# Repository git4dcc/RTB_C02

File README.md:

# RTB_C02

My C02 module is designed to trace DCC Railcom traffic for decoder debugging and development purposes. In particular the Railcom capture is an important feature and helps to validate if a decoders is RCN-217 compliant. The C02 uses the Vt100 terminal emulation control codes for its user interface. Therefore a VT100 capeable terminal program is a must (e.g. putty, teraterm). The USB interface is galvanically isolated from the DCC track potential.

<details>
<summary>User Guides</summary>

- [User Guide - DE](https://rtb4dcc.de/DPM_User_Guide_de)<br>
- User Guide - EN

</details>

<br>

# Hardware
My current PCB layout uses SMD footprints with 0.5mm pitch and mostly 0603 but some 0402 parts. Reflow soldering is my recommendation, but with some experience handsoldering may also be possible.

## PCB
- 4-layer PCB, FR4, 1.6mm
- CPU: mega328pb
- USB: FT232x (Mini-B)
- DC/DC: NME0505SC (or compatible)

## Kicad
[Schematic](doc/C02_schematic.pdf) | [Layout](doc/C02_layout.pdf) | [Gerber](gerber/)

<details>
<summary>Dependency</summary>
<br>
  
:yellow_circle: Requires my Kicad project library [RTB_SamacSys](/../../../../git4dcc/RTB_SamacSys) in the same directory tree.

</details>

## Firmware
Filename structure: { **pcb** }{ **code** }{ **version** }.hex

Example: **C02F0001**.hex

|   | Description |
| --- | --- |
| **pcb** | Name of matching hardware (**C02**) |
| **code** | Type of code contained (**R**=rom, **B**=bootloader, **F**=flash, **U**=bld update, **P**=UPDI/SPI factory code) |
| **version** | Release version (**####**) |

## ISP
The fuse settings as well as the P-code (C02Pxxxx.hex) has to be installed by using the ISP.<br>

<details>
<summary>Details</summary>
<br>

> **CAUTION:** Before connecting the ISP, the jumper next to the ISP 6-pin interface must be closed (yellow jumper on picture).

<br>

| Fuses Setting | Bootloader Install |
| --- | --- |
|||

</details>

## Bootloader
Subsequent main code updates can be done via uploading the new firmware (C02Fxxxx.hex) file to the bootloader console prompt.<br>

<details>
<summary>Details</summary>

- press F1 to switch to console screen
- press ^b (ctrl-b) to enter bootloader
- upload the firmware file (C02Fxxxx.hex)
- press x to exit the bootloader

</details>

# Software
Operating the C02 is within the terminal window.
## Terminal screens
Below some example screens of the different functional sections. The screens (called aspects) can be switched by pressing F1-F7.
All screens are updated in real-time speed, ensuring always up-to-date information shown.

| Aspect | Example |
| --- | --- |
| **F1:** Console prompt. |  |
| **F2:** DCC/Railcom line by line real-time trace. |  |
| **F3:** DCC/Railcom decoder payload |  |
| **F4:** DCC/Railcom timing<br> |  |
| **F5:** DCC command set |  |
| **F6:** Railcom response set |  |

# Images
This is how the PCB looks like.<br><br>

# YouTube
Some short videos to see the DCC/Railcom logger in action.<br><br>

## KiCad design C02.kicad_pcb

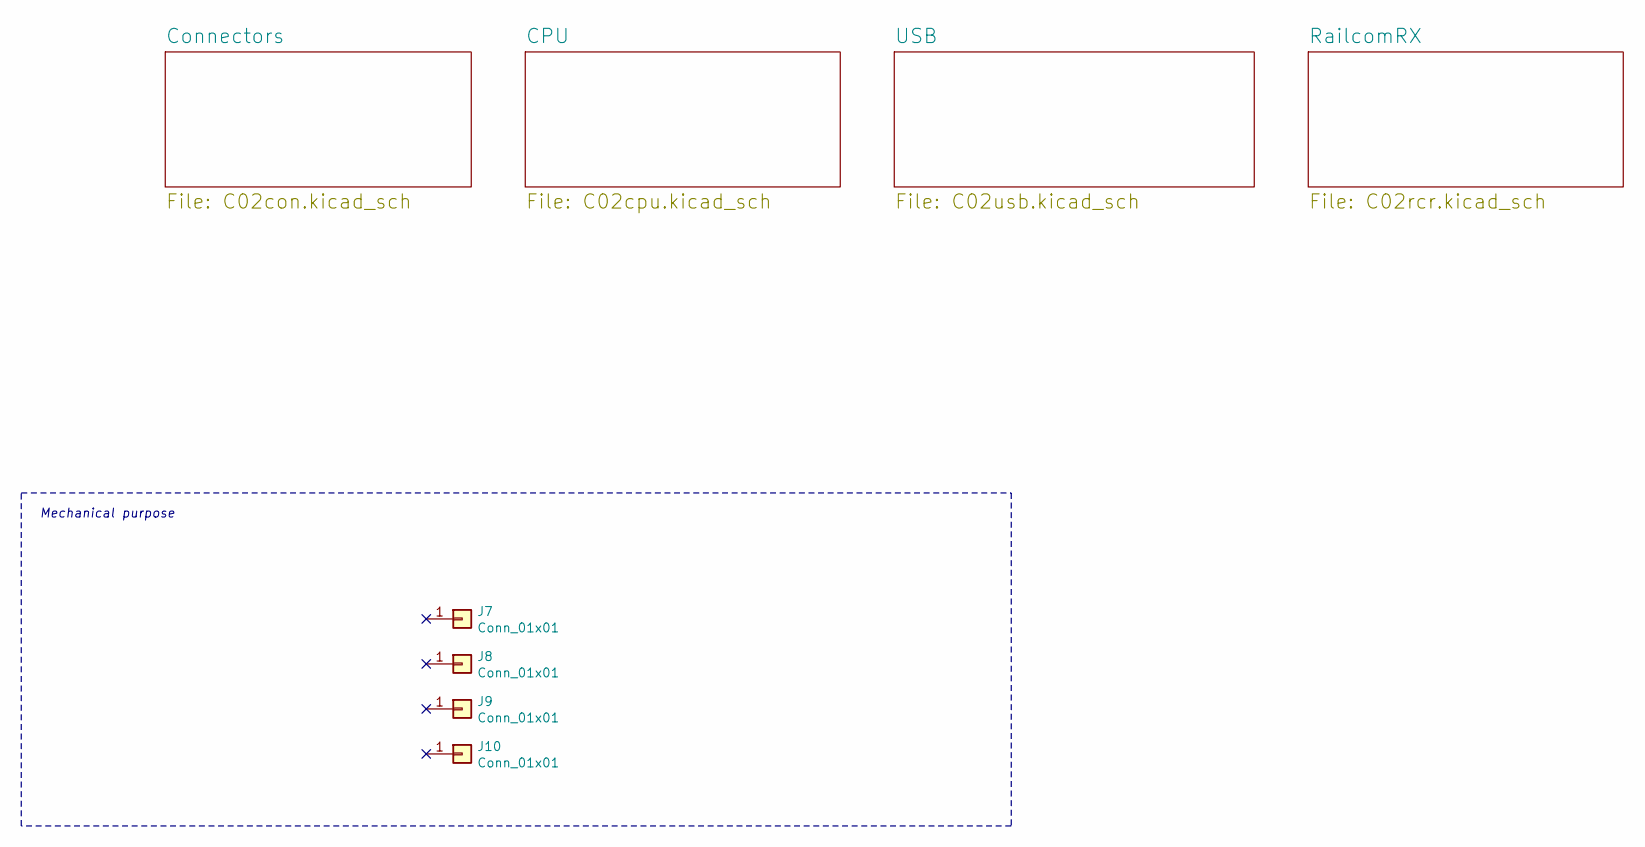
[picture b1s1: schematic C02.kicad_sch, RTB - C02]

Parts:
J7, J8, J9, J10: Conn_01x01; MountingHole_3.2mm_M3_Pad

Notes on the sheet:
Mechanical purpose

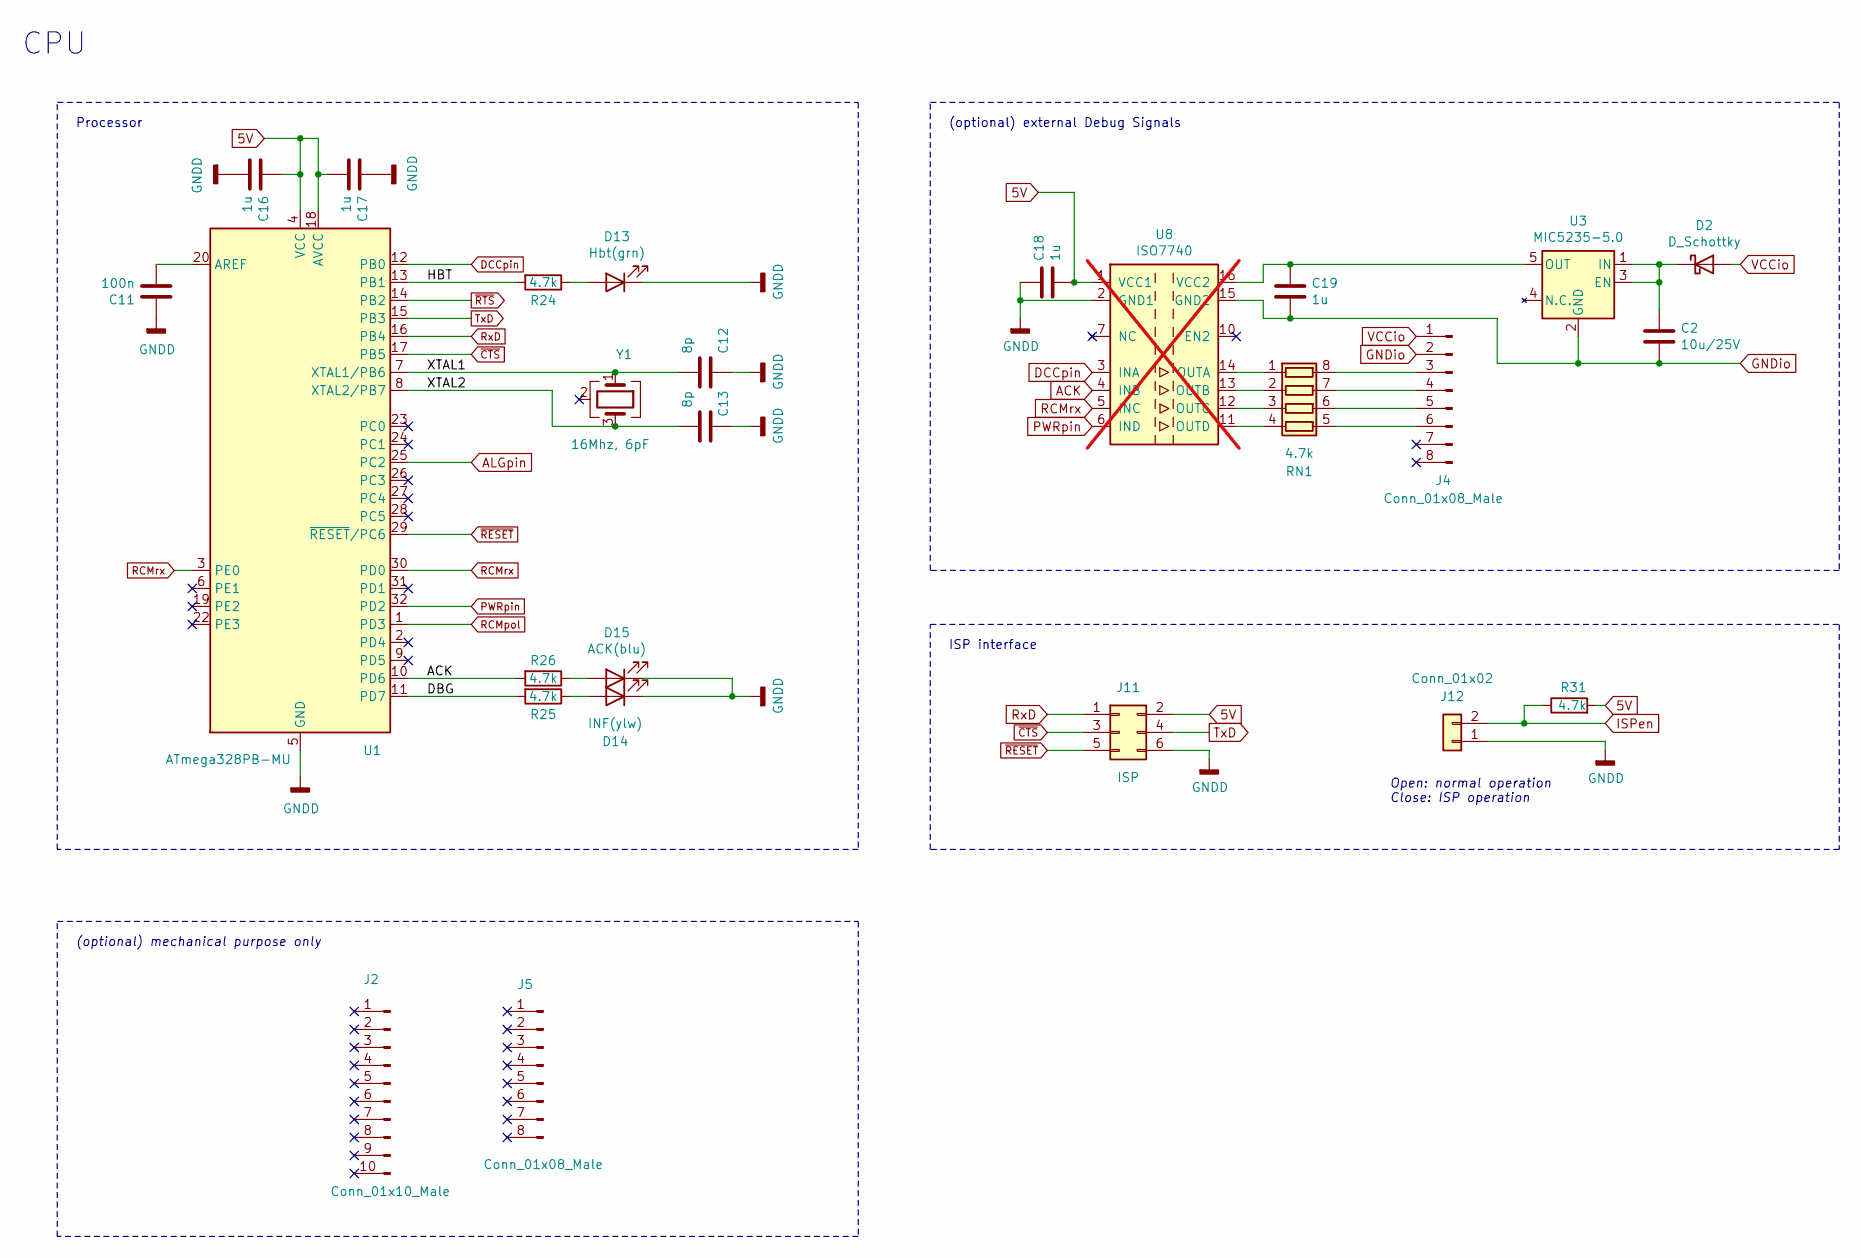
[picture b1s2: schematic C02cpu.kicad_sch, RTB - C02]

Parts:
C2: 10u/25V; C_0603_1608Metric; LCSC Part # C96446
C11: 100n; C_0603_1608Metric; LCSC Part # C14663
C12, C13: 8p; C_0402_1005Metric; LCSC Part # C32949
C16, C17, C18, C19: 1u; C_0603_1608Metric; LCSC Part # C15849
D2: D_Schottky; D_0603_1608Metric; LCSC Part # C143804
D13: Hbt(grn); LED_0603_1608Metric; LCSC Part # C2289
D14: INF(ylw); LED_0603_1608Metric; LCSC Part # C2287
D15: ACK(blu); LED_0603_1608Metric; LCSC Part # C2288
J2: Conn_01x10_Male; PinHeader_1x10_P2.54mm_Vertical
J4, J5: Conn_01x08_Male; PinHeader_1x08_P2.54mm_Vertical
J11: ISP; PinHeader_2x03_P2.54mm_Vertical
J12: Conn_01x02; PinHeader_1x02_P2.54mm_Vertical
R24, R25, R26, R31: 4.7k; R_0603_1608Metric; LCSC Part # C23162
RN1: 4.7k; R_Array_Concave_4x0603; LCSC Part # C66697
U1: ATmega328PB-MU; QFN-32-1EP_5x5mm_P0.5mm_EP3.1x3.1mm; LCSC Part # C967933
U3: MIC5235-5.0; SOT-23-5; LCSC Part # C7202996
U8: ISO7740; SSOP-16_3.9x4.9mm_P0.635mm; LCSC Part # C5216473; not fitted
Y1: 16Mhz, 6pF; Crystal_SMD_2016-4Pin_2.0x1.6mm; LCSC Part # C1986052

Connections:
5V: C16.2, C17.1, C18.1, J11.2, R31.2, U1.4 (VCC), U1.18 (AVCC), U8.1 (VCC1); also elsewhere on the board
/CPU/DBG: R25.2, U1.11 (PD7)
/CPU/HBT: R24.2, U1.13 (PB1)
/CPU/XTAL1: C12.2, U1.7 (XTAL1/PB6), Y1.1
/CPU/XTAL2: C13.2, U1.8 (XTAL2/PB7), Y1.3
ACK: R26.2, U1.10 (PD6), U8.4 (INB)
ALGpin: U1.25 (PC2); also elsewhere on the board
DCCpin: U1.12 (PB0), U8.3 (INA); also elsewhere on the board
GNDD: C11.2, C12.1, C13.1, C16.1, C17.2, C18.2, D13.1 (K), D14.1 (K), D15.1 (K), J11.6, J12.1, U1.5 (GND), U1.21 (GND), U1.33, U8.2 (GND1), U8.8 (GND1); also elsewhere on the board
GNDio: C2.1, C19.1, J4.2, U3.2 (GND), U8.9 (GND2), U8.15 (GND2)
ISPen: J12.2, R31.1; also elsewhere on the board
unnamed: C2.2, D2.1 (K), U3.1 (IN), U3.3 (EN)
unnamed: D13.2 (A), R24.1
unnamed: D14.2 (A), R25.1
unnamed: D15.2 (A), R26.1
unnamed: J4.3, RN1.8 (R1.2)
unnamed: J4.4, RN1.7 (R2.2)
unnamed: J4.5, RN1.6 (R3.2)
unnamed: J4.6, RN1.5 (R4.2)
unnamed: RN1.1 (R1.1), U8.14 (OUTA)
unnamed: RN1.2 (R2.1), U8.13 (OUTB)
unnamed: RN1.3 (R3.1), U8.12 (OUTC)
unnamed: RN1.4 (R4.1), U8.11 (OUTD)
unnamed: C11.1, U1.20 (AREF)
unnamed: C19.2, U3.5 (OUT), U8.16 (VCC2)
PWRpin: U1.32 (PD2), U8.6 (IND); also elsewhere on the board
RCMpol: U1.1 (PD3); also elsewhere on the board
RCMrx: U1.3 (PE0), U1.30 (PD0), U8.5 (INC); also elsewhere on the board
RxD: J11.1, U1.16 (PB4); also elsewhere on the board
TxD: J11.4, U1.15 (PB3); also elsewhere on the board
VCCio: D2.2 (A), J4.1
~CTS: J11.3, U1.17 (PB5); also elsewhere on the board
~RESET: J11.5, U1.29 (~RESET/PC6)
~RTS: U1.14 (PB2); also elsewhere on the board

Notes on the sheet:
Processor
Open: normal operation Close: ISP operation
ISP interface
(optional) mechanical purpose only
CPU
(optional) external Debug Signals

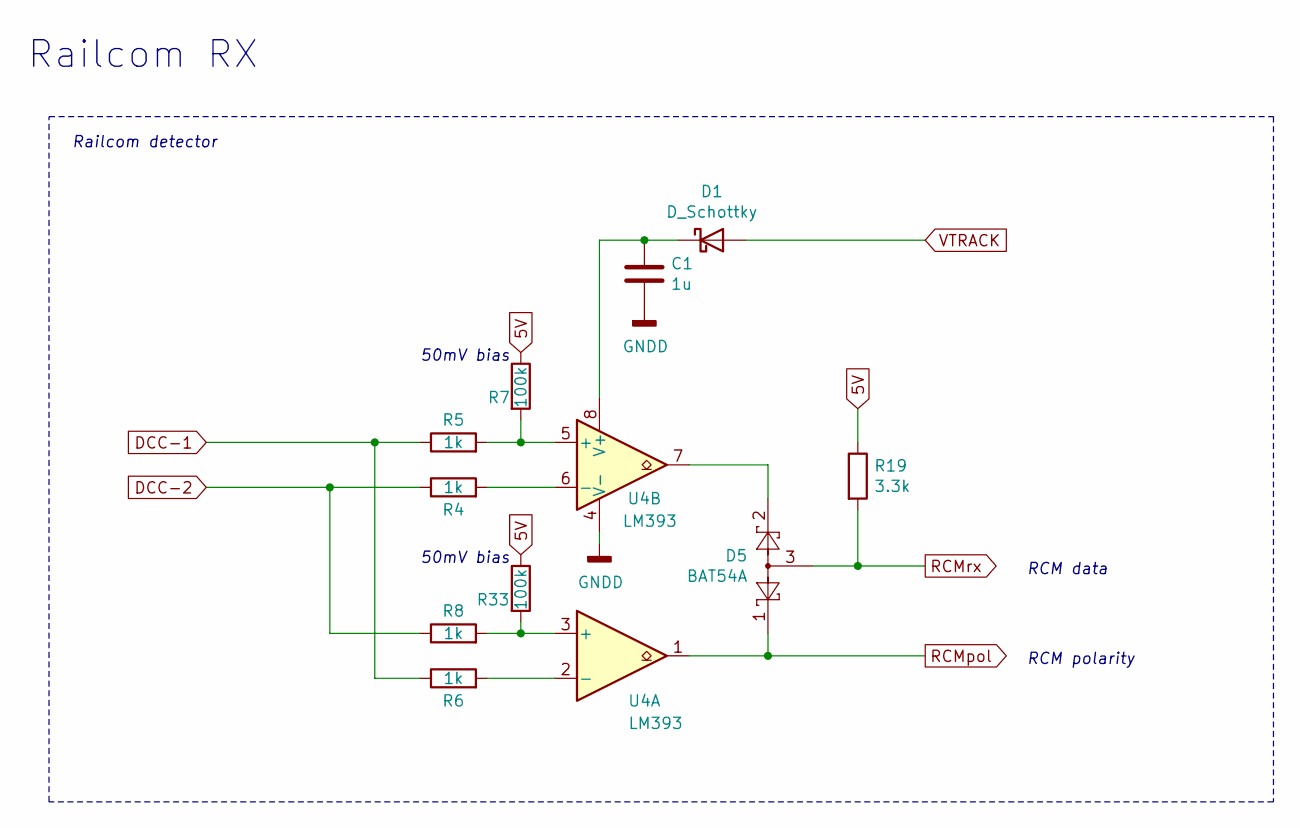
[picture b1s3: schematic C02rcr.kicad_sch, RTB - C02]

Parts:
C1: 1u; C_0603_1608Metric; LCSC Part # C15849
D1: D_Schottky; D_0603_1608Metric
D5: BAT54A; SOT-323_SC-70; LCSC Part # C78261
R4, R5, R6, R8: 1k; R_0603_1608Metric; LCSC Part # C21190
R7, R33: 100k; R_0603_1608Metric; LCSC Part # C25803
R19: 3.3k; R_0603_1608Metric; LCSC Part # C22978
U4: LM393; DFN-8_2x2mm_P0.5mm; LCSC Part # C2970927

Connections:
5V: R7.1, R19.1, R33.1; also elsewhere on the board
DCC-1: R5.1, R6.1; also elsewhere on the board
DCC-2: R4.1, R8.1; also elsewhere on the board
GNDD: C1.2, U4.4 (V-); also elsewhere on the board
unnamed: C1.1, D1.1 (K), U4.8 (V+)
unnamed: D5.2, U4.7
unnamed: R8.2, R33.2, U4.3 (+)
unnamed: R6.2, U4.2 (-)
unnamed: R5.2, R7.2, U4.5 (+)
unnamed: R4.2, U4.6 (-)
RCMpol: D5.1, U4.1; also elsewhere on the board
RCMrx: D5.3, R19.2; also elsewhere on the board
VTRACK: D1.2 (A); also elsewhere on the board

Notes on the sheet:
RCM polarity
50mV bias
Railcom detector
Railcom RX
RCM data

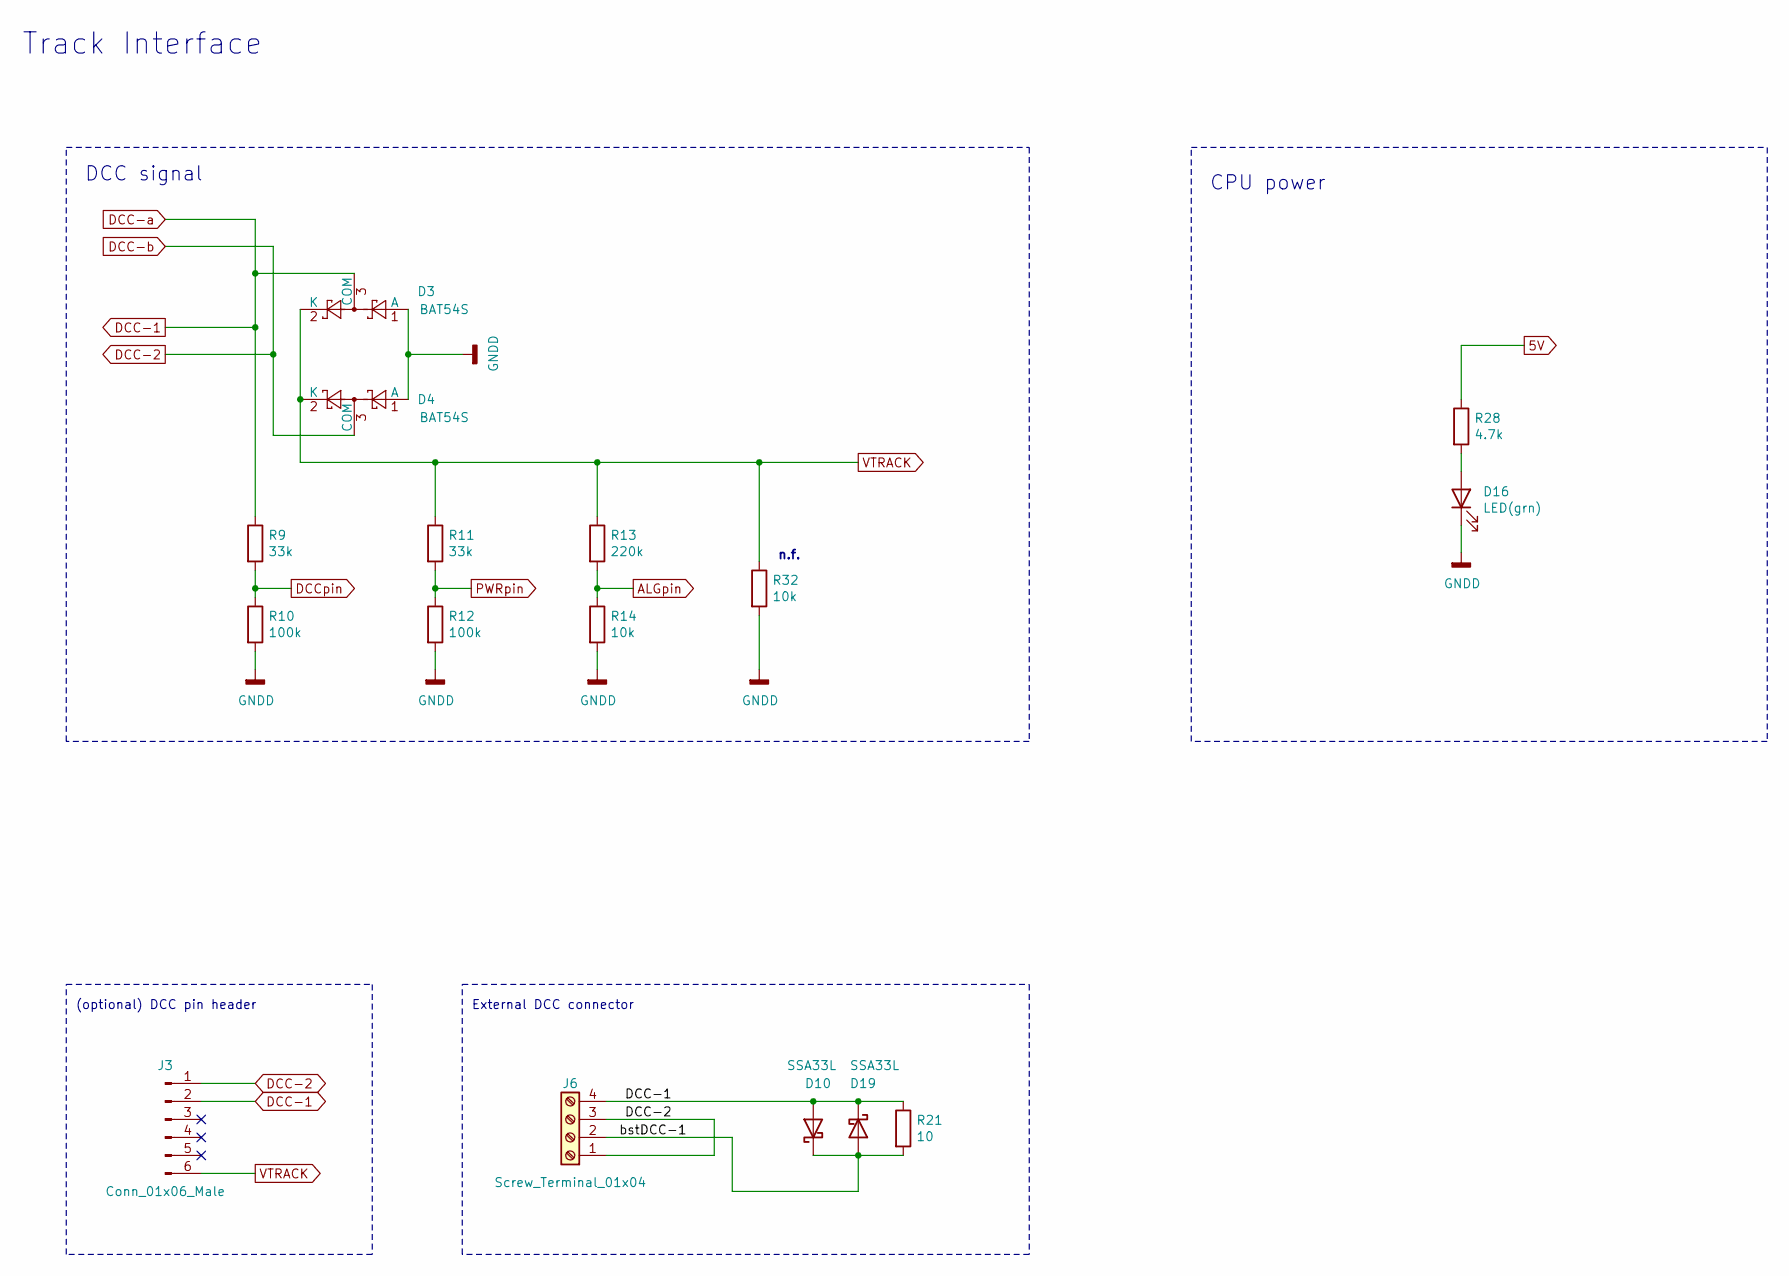
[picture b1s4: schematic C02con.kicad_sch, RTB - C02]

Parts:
D3, D4: BAT54S; SOT-323_SC-70; LCSC Part # C78606
D10, D19: SSA33L; D_SMA; LCSC Part # C435944
D16: LED(grn); LED_0603_1608Metric; LCSC Part # C2289
J3: Conn_01x06_Male; PinHeader_1x06_P2.54mm_Vertical
J6: Screw_Terminal_01x04; TerminalBlock_RND_205-00003_1x04_P5.00mm_Horizontal
R9, R11: 33k; R_0603_1608Metric; LCSC Part # C4216
R10, R12: 100k; R_0603_1608Metric; LCSC Part # C25803
R13: 220k; R_0603_1608Metric; LCSC Part # C22961
R14, R32: 10k; R_0603_1608Metric; LCSC Part # C25804
R21: 10; R_0603_1608Metric; LCSC Part # C22859
R28: 4.7k; R_0603_1608Metric; LCSC Part # C23162

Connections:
5V: R28.1; also elsewhere on the board
/Connectors/bstDCC-1: D10.1 (K), D19.2 (A), J6.2, R21.2
ALGpin: R13.2, R14.1; also elsewhere on the board
DCC-1: D3.3 (COM), D10.2 (A), D19.1 (K), J3.2, J6.4, R9.1, R21.1; also elsewhere on the board
DCC-2: D4.3 (COM), J3.1, J6.1, J6.3; also elsewhere on the board
DCCpin: R9.2, R10.1; also elsewhere on the board
GNDD: D3.1 (A), D4.1 (A), D16.1 (K), R10.2, R12.2, R14.2, R32.2; also elsewhere on the board
unnamed: D16.2 (A), R28.2
PWRpin: R11.2, R12.1; also elsewhere on the board
VTRACK: D3.2 (K), D4.2 (K), J3.6, R11.1, R13.1, R32.1; also elsewhere on the board

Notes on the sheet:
Track Interface
(optional) DCC pin header
CPU power
DCC signal
External DCC connector
n.f.

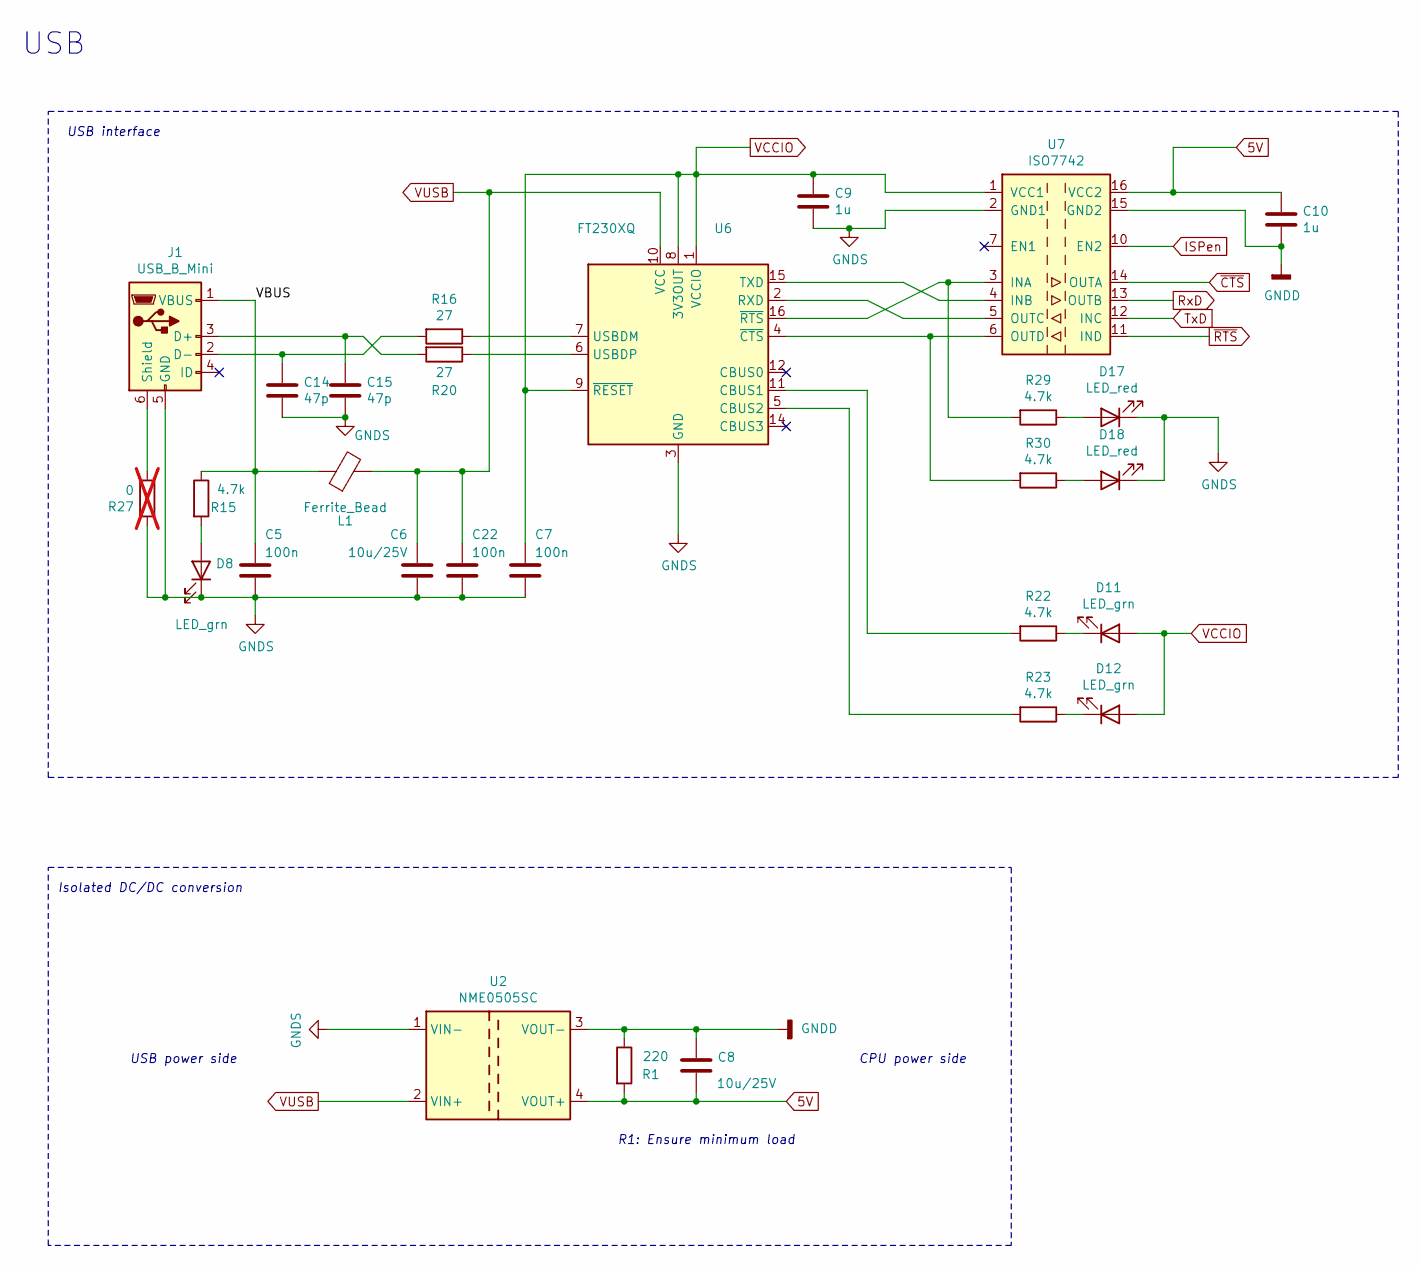
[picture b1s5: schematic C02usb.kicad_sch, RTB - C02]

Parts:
C5, C7, C22: 100n; C_0603_1608Metric; LCSC Part # C14663
C6, C8: 10u/25V; C_0603_1608Metric; LCSC Part # C96446
C9, C10: 1u; C_0603_1608Metric; LCSC Part # C15849
C14, C15: 47p; C_0603_1608Metric; LCSC Part # C1671
D8, D11, D12: LED_grn; LED_0603_1608Metric; LCSC Part # C2289
D17, D18: LED_red; LED_0603_1608Metric; LCSC Part # C125099
J1: USB_B_Mini; USB_Micro-B_Reichelt_BWM_SMD; LCSC Part # C2688795
L1: Ferrite_Bead; L_0805_2012Metric; LCSC Part # C1017
R1: 220; R_0805_2012Metric; LCSC Part # C17557
R15, R22, R23, R29, R30: 4.7k; R_0603_1608Metric; LCSC Part # C23162
R16, R20: 27; R_0603_1608Metric; LCSC Part # C23345
R27: 0; R_0603_1608Metric; LCSC Part # C21189; not fitted
U2: NME0505SC; DCDC-Conv_muRata_NMAxxxxSC
U6: FT230XQ; QFN-16-1EP_4x4mm_P0.65mm_EP2.5x2.5mm; LCSC Part # C3216402
U7: ISO7742; SSOP-16_3.9x4.9mm_P0.635mm; LCSC Part # C5216468

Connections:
5V: C8.1, C10.2, R1.2, U2.4 (VOUT+), U7.16 (VCC2); also elsewhere on the board
/USB/VBUS: C5.2, J1.1 (VBUS), L1.1, R15.1
GNDD: C8.2, C10.1, R1.1, U2.3 (VOUT-), U7.9 (GND2), U7.15 (GND2); also elsewhere on the board
GNDS: C5.1, C6.2, C7.1, C9.1, C14.1, C15.1, C22.1, D8.1 (K), D17.1 (K), D18.1 (K), J1.5 (GND), R27.2, U2.1 (VIN-), U6.3 (GND), U6.13 (GND), U6.17 (GND), U7.2 (GND1), U7.8 (GND1)
ISPen: U7.10 (EN2); also elsewhere on the board
unnamed: D8.2 (A), R15.2
unnamed: D11.1 (K), R22.1
unnamed: D12.1 (K), R23.1
unnamed: D17.2 (A), R29.1
unnamed: D18.2 (A), R30.1
unnamed: C15.2, J1.3 (D+), R20.2
unnamed: C14.2, J1.2 (D-), R16.2
unnamed: J1.6 (Shield), R27.1
unnamed: R22.2, U6.11 (CBUS1)
unnamed: R23.2, U6.5 (CBUS2)
unnamed: U6.2 (RXD), U7.5 (OUTC)
unnamed: U6.15 (TXD), U7.4 (INB)
unnamed: R16.1, U6.7 (USBDM)
unnamed: R20.1, U6.6 (USBDP)
unnamed: R30.2, U6.4 (~CTS), U7.6 (OUTD)
unnamed: R29.2, U6.16 (~RTS), U7.3 (INA)
RxD: U7.13 (OUTB); also elsewhere on the board
TxD: U7.12 (INC); also elsewhere on the board
VCCIO: C7.2, C9.2, D11.2 (A), D12.2 (A), U6.1 (VCCIO), U6.8 (3V3OUT), U6.9 (~RESET), U7.1 (VCC1)
VUSB: C6.1, C22.2, L1.2, U2.2 (VIN+), U6.10 (VCC)
~CTS: U7.14 (OUTA); also elsewhere on the board
~RTS: U7.11 (IND); also elsewhere on the board

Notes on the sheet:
Isolated DC/DC conversion
USB
R1: Ensure minimum load
USB interface
USB power side
CPU power side

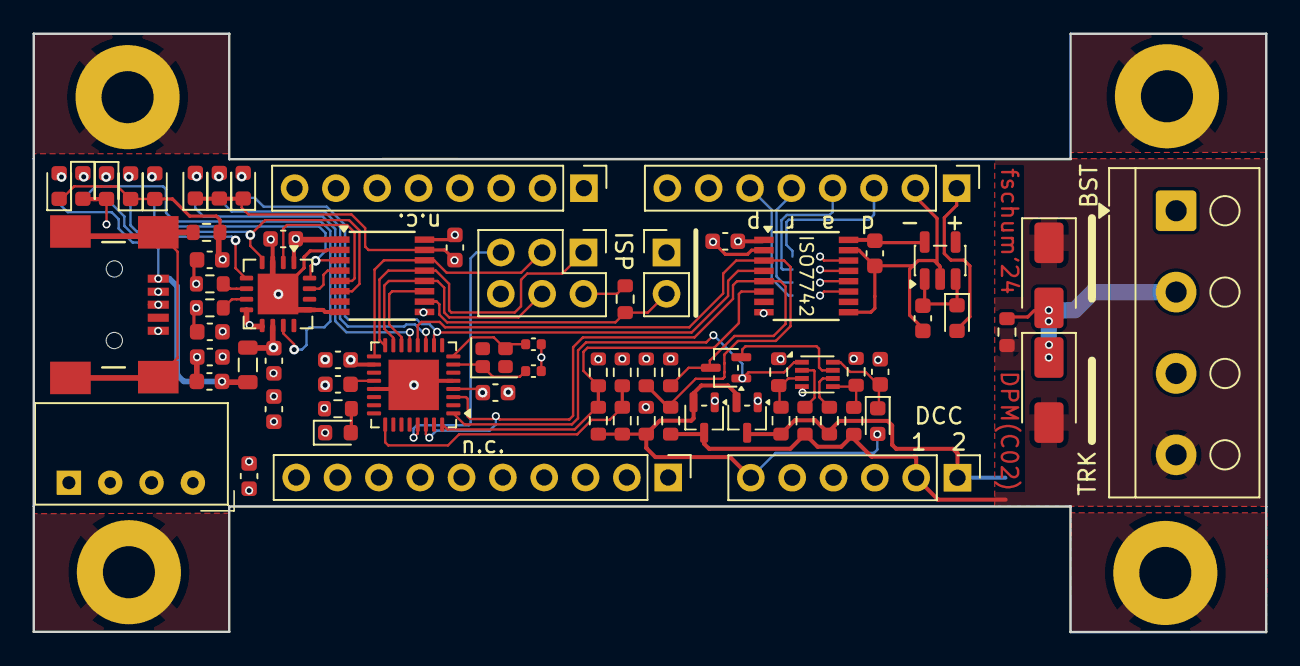
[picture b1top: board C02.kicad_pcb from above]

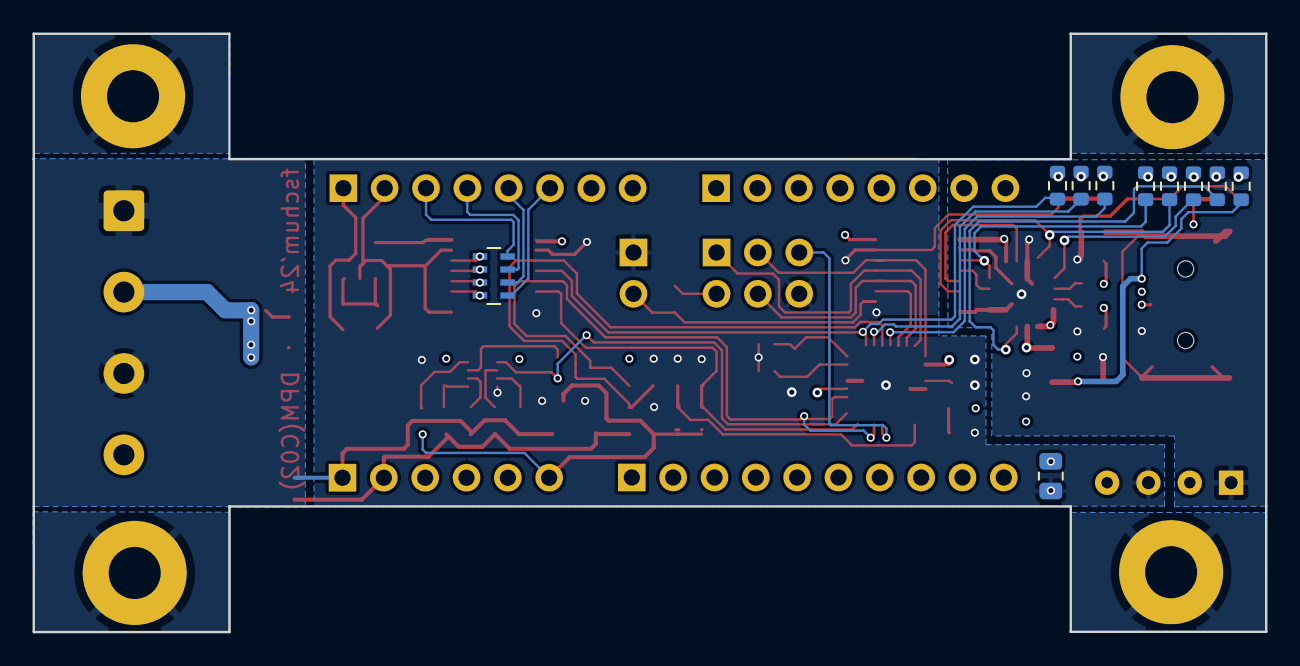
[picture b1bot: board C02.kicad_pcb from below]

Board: 4 copper layers, 75.7 x 36.8 mm, 85 parts (10 on the bottom side), 65 nets.

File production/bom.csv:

Designator,Footprint,Quantity,Value,LCSC Part #
"C1, C10, C16, C17, C18, C19, C9",0603,7,1u,C15849
"C11, C22, C5, C7",0603,4,100n,C14663
"C12, C13",0402,2,8p,C32949
"C14, C15",0603,2,47p,C1671
"C2, C6, C8",0603,3,10u/25V,C96446
D1,0603,1,D_Schottky,
"D10, D19",D_SMA,2,SSA33L,C435944
"D11, D12, D8",0603,3,LED_grn,C2289
D13,0603,1,Hbt(grn),C2289
D14,0603,1,INF(ylw),C2287
D15,0603,1,ACK(blu),C2288
D16,0603,1,LED(grn),C2289
"D17, D18",0603,2,LED_red,C125099
D2,0603,1,D_Schottky,C143804
"D3, D4",SOT-323_SC-70,2,BAT54S,C78606
D5,SOT-323_SC-70,1,BAT54A,C78261
J1,USB_Micro-B_Reichelt_BWM_SMD,1,USB_B_Mini,C2688795
"J10, J7, J8, J9",MountingHole_3.2mm_M3_Pad,4,Conn_01x01,
J11,PinHeader_2x03_P2.54mm_Vertical,1,ISP,
J12,PinHeader_1x02_P2.54mm_Vertical,1,Conn_01x02,
J2,PinHeader_1x10_P2.54mm_Vertical,1,Conn_01x10_Male,
J3,PinHeader_1x06_P2.54mm_Vertical,1,Conn_01x06_Male,
"J4, J5",PinHeader_1x08_P2.54mm_Vertical,2,Conn_01x08_Male,
J6,TerminalBlock_RND_205-00003_1x04_P5.00mm_Horizontal,1,Screw_Terminal_01x04,
L1,0805,1,Ferrite_Bead,C1017
R1,0805,1,220,C17557
"R10, R12, R33, R7",0603,4,100k,C25803
"R11, R9",0603,2,33k,C4216
R13,0603,1,220k,C22961
"R14, R32",0603,2,10k,C25804
"R15, R22, R23, R24, R25, R26, R28, R29, R30, R31",0603,10,4.7k,C23162
"R16, R20",0603,2,27,C23345
R19,0603,1,3.3k,C22978
R21,0603,1,10,C22859
"R4, R5, R6, R8",0603,4,1k,C21190
RN1,R_Array_Concave_4x0603,1,4.7k,C66697
U1,QFN-32-1EP_5x5mm_P0.5mm_EP3.1x3.1mm,1,ATmega328PB-MU,C967933
U2,DCDC-Conv_muRata_NMAxxxxSC,1,NME0505SC,
U3,SOT-23-5,1,MIC5235-5.0,C7202996
U4,DFN-8_2x2mm_P0.5mm,1,LM393,C2970927
U6,QFN-16-1EP_4x4mm_P0.65mm_EP2.5x2.5mm,1,FT230XQ,C3216402
U7,SSOP-16_3.9x4.9mm_P0.635mm,1,ISO7742,C5216468
Y1,Crystal_SMD_2016-4Pin_2.0x1.6mm,1,"16Mhz, 6pF",C1986052

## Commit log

2024-10-04 Added local images
2026-02-20 Update links in README for user guides and dependencies
2026-02-20 git mirror test
2026-02-25 mod: add JLCPCB part numbers

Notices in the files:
C02.kicad_pcb:
Licensed under the Apache License, Version 2.0
README.md:
Apache License 2.0
